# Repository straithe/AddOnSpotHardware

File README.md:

# AddOnSpot
A shitty add-on (SAO) that has a light that changes between red, yellow, and green.

## Description
The intended purpose for this SAO is for people to be able to indicate their social boundries in public settings. The inspiration for this project comes from a [tweet](https://twitter.com/k8em0/status/1156100010657718272) by [k8emo](https://twitter.com/k8em0) and a [project](https://medium.com/@elkentaro/ledify-you-life-color-changing-tiara-build-f12cb3d7741) by [elkentaro](https://twitter.com/elkentaro).

The three colours of light (red, yellow, and green) can be used by the user to indicate three different things:
* red means that they not want anyone to approach them at that time,
* yellow means that they are only open to people they know approaching them, 
* green means that they are open to anyone coming up to say 'hi!'.

## Design Considerations
* This SAO was designed to control the LEDs in two ways depending on what the user desires. :

  * The first (and suggested) way to control the LEDs is with the two switches that are provided on the SAO. One of the switches turns on the red LED and the other turns on the green LED. If the user turns on both of the switches the LED will be yellow.
  
  * The second way to control the LEDs is from the board the SAO is attached to. Controlling the LEDs on the SAO from the board it is attached to can be done through the GPIO1 and GPIO2 pins (pins 1&2 on the rectangular connector in the schematic). If the user wants to control the LEDs with the GPIO pins, they will need to populate the resistors between the GPIO pins and the LEDs. The reason that the resistors from the GPIO pins are not populated by default is because sometimes GPIO pins are pulled up by default. If the connection point from the GPIO pins were between the switches and their resistors, the LEDs would always be dimly on, thus making it difficult to display just red or just green, or to turn the SAO off. 

* The switches that were chosen were picked for their extended actuator length. The hope is that an extended actuator length will make it easier for people with long fingernails using the SAO to turn the lights on and off.

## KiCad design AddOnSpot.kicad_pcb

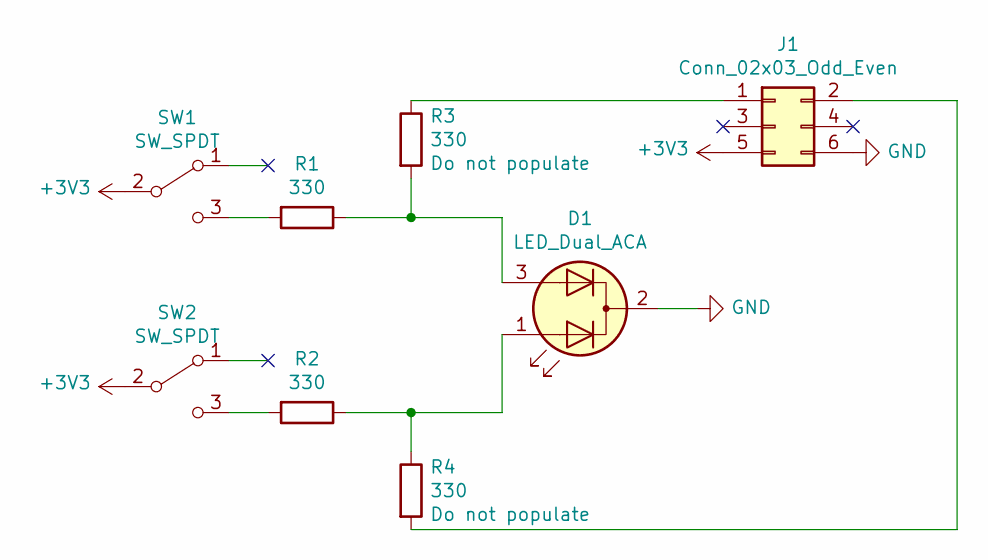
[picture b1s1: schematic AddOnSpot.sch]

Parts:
D1: LED_Dual_ACA; LED_D10.0mm-3; Part Number 4042
J1: Conn_02x03_Odd_Even; PinHeader_2x03_P2.54mm_Vertical; Part Number 61200621621
R1, R2, R3, R4: 330; R_Axial_DIN0207_L6.3mm_D2.5mm_P10.16mm_Horizontal
SW1, SW2: SW_SPDT; SW_Slide_1P2T_CK_OS102011MS2Q; Part Number SK-12F17-G 7

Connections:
+3V3: J1.5, SW1.2 (B), SW2.2 (B)
GND: D1.2 (K), J1.6
unnamed: D1.1 (A1), R2.1, R4.1
unnamed: D1.3 (A2), R1.1, R3.2
unnamed: J1.1, R3.1
unnamed: J1.2, R4.2
unnamed: R1.2, SW1.3 (C)
unnamed: R2.2, SW2.3 (C)

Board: 2 copper layers, 8 parts (0 on the bottom side), 8 nets, no tracks yet.

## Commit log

2019-10-29 Added initial design files.
